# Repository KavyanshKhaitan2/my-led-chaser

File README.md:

# my-led-chaser
Just a simple LED chaser I made using the guides for Blinky @ Hack Club Blueprint.
# PCB View

# JLCPCB Order page

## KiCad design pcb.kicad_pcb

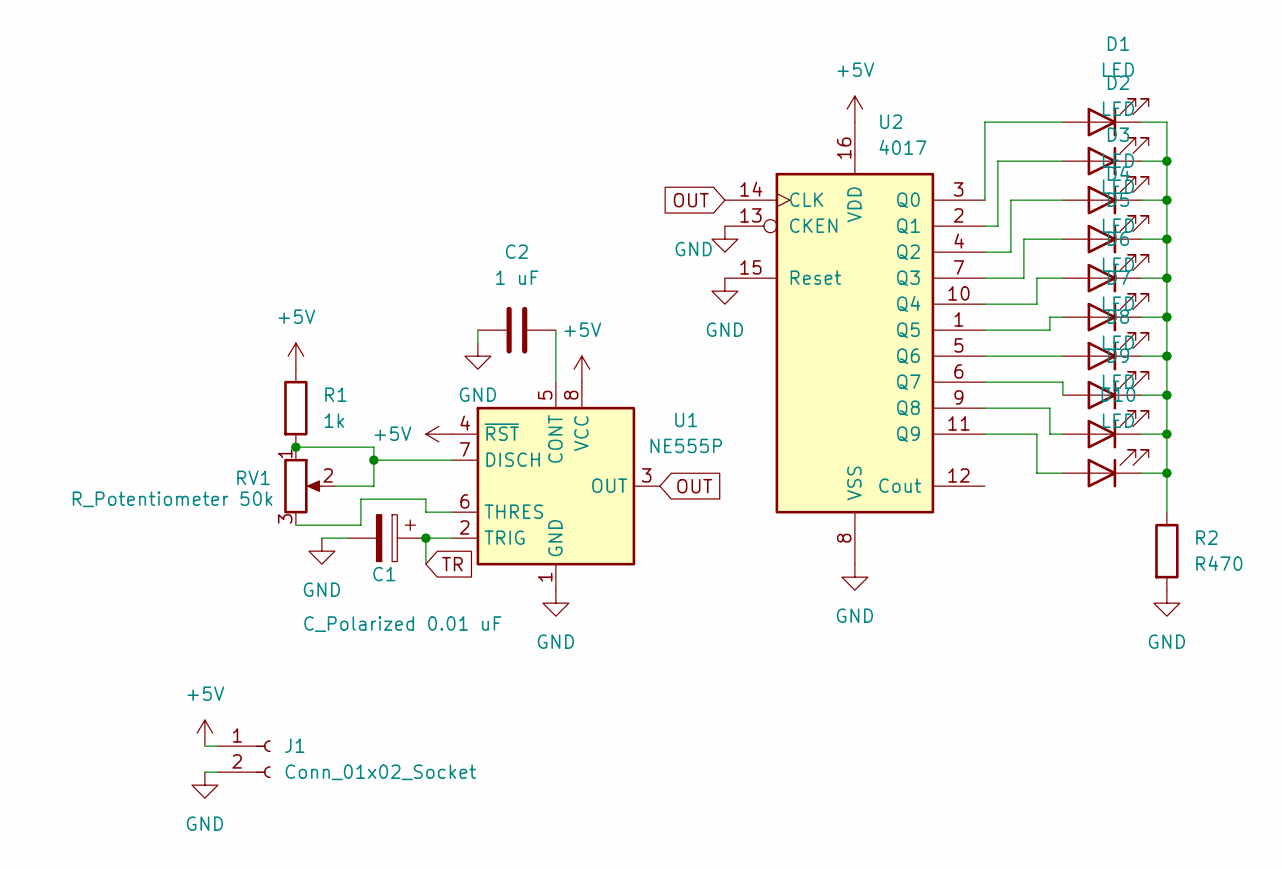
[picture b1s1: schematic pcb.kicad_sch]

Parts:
C1: C_Polarized 0.01 uF; CP_Radial_D5.0mm_P2.00mm
C2: 1 uF; C_Disc_D7.5mm_W2.5mm_P5.00mm
D1, D2, D3, D4, D5, D6, D7, D8, D9, D10: LED; LED_D3.0mm
J1: Conn_01x02_Socket; PinHeader_1x02_P2.54mm_Vertical
R1: 1k; R_Axial_DIN0207_L6.3mm_D2.5mm_P7.62mm_Horizontal
R2: R470; R_Axial_DIN0207_L6.3mm_D2.5mm_P7.62mm_Horizontal
RV1: R_Potentiometer 50k; Potentiometer_Vishay_T93YA_Vertical
U1: NE555P; DIP-8_W7.62mm
U2: 4017; N16

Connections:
+5V: J1.1, R1.1, U1.4 (~RST), U1.8 (VCC), U2.16 (VDD)
GND: C1.2, C2.1, J1.2, R2.2, U1.1 (GND), U2.8 (VSS), U2.13 (CKEN), U2.15 (Reset)
unnamed: D1.2 (A), U2.3 (Q0)
unnamed: D1.1 (K), D2.1 (K), D3.1 (K), D4.1 (K), D5.1 (K), D6.1 (K), D7.1 (K), D8.1 (K), D9.1 (K), D10.1 (K), R2.1
unnamed: D2.2 (A), U2.2 (Q1)
unnamed: D3.2 (A), U2.4 (Q2)
unnamed: D4.2 (A), U2.7 (Q3)
unnamed: D5.2 (A), U2.10 (Q4)
unnamed: D6.2 (A), U2.1 (Q5)
unnamed: D7.2 (A), U2.5 (Q6)
unnamed: D8.2 (A), U2.6 (Q7)
unnamed: D9.2 (A), U2.9 (Q8)
unnamed: D10.2 (A), U2.11 (Q9)
unnamed: C2.2, U1.5 (CONT)
unnamed: R1.2, RV1.1, RV1.2, U1.7 (DISCH)
unnamed: RV1.3, U1.6 (THRES)
OUT: U1.3 (OUT), U2.14 (CLK)
TR: C1.1, U1.2 (TRIG)

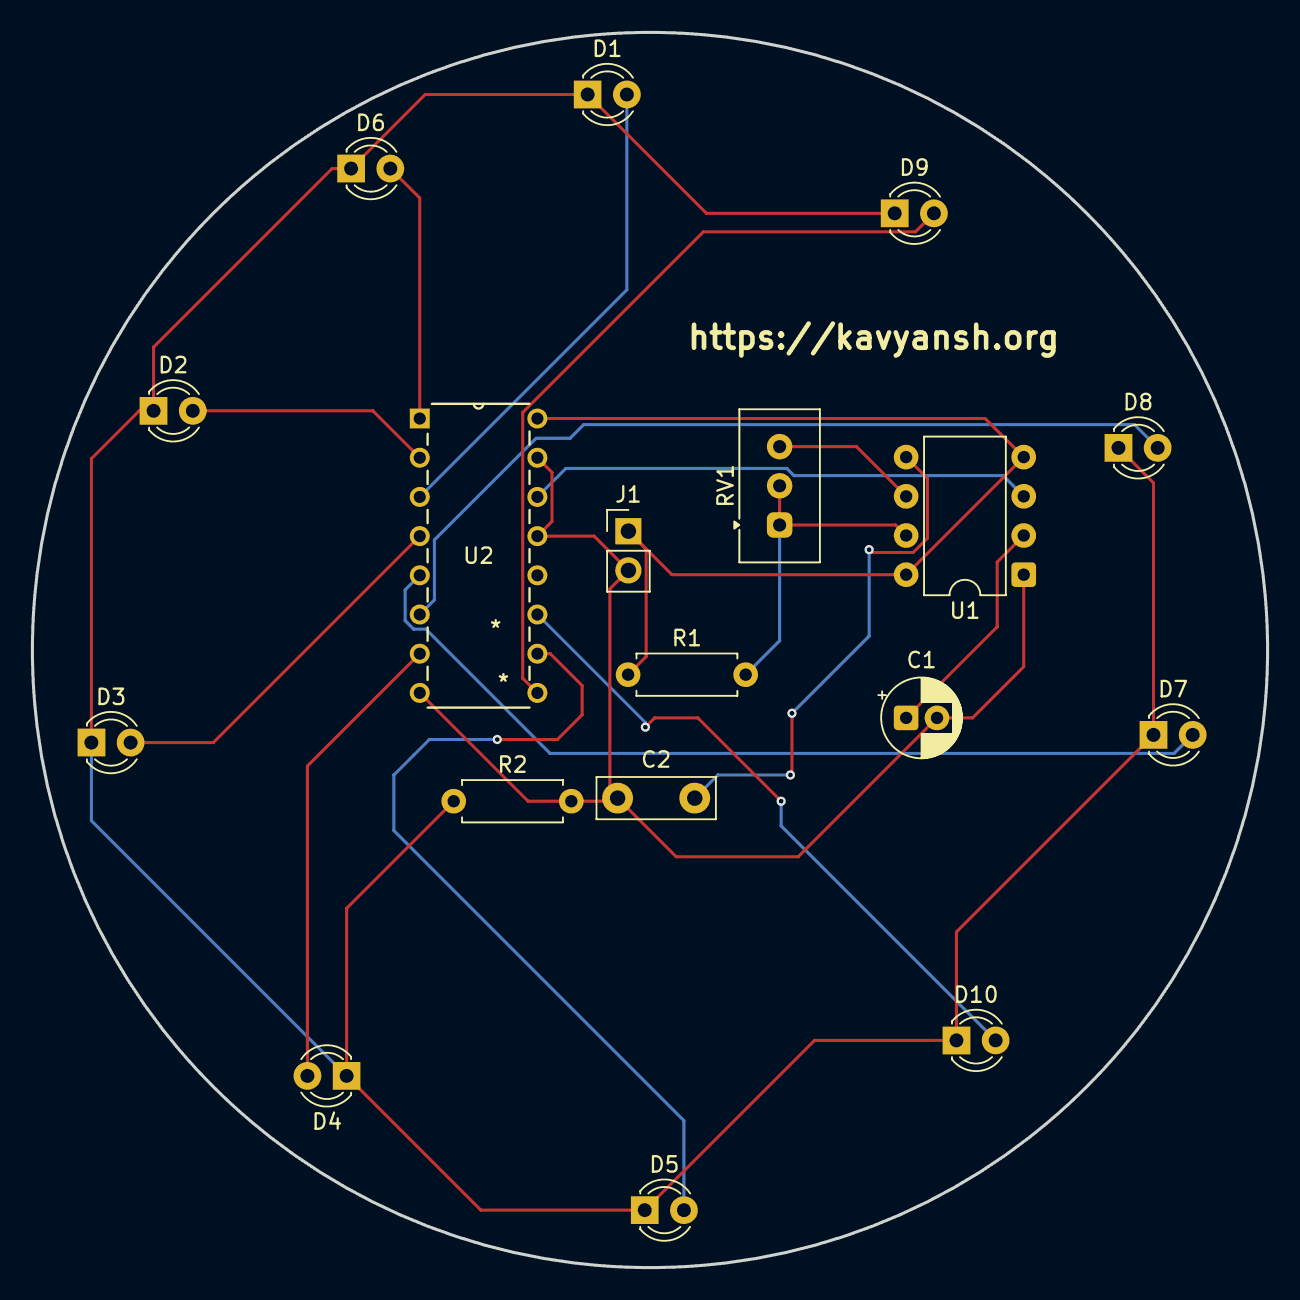
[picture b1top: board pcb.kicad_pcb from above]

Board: 2 copper layers, 80.0 x 80.0 mm, 18 parts (0 on the bottom side), 18 nets.

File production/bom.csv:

Designator,Footprint,Quantity,Value,LCSC Part #
C1,CP_Radial_D5.0mm_P2.00mm,1,C_Polarized 0.01 uF,
C2,C_Disc_D7.5mm_W2.5mm_P5.00mm,1,1 uF,
"D1, D10, D2, D3, D4, D5, D6, D7, D8, D9",LED_D3.0mm,10,LED,
J1,PinHeader_1x02_P2.54mm_Vertical,1,Conn_01x02_Socket,
R1,R_Axial_DIN0207_L6.3mm_D2.5mm_P7.62mm_Horizontal,1,1k,
R2,R_Axial_DIN0207_L6.3mm_D2.5mm_P7.62mm_Horizontal,1,R470,
RV1,Potentiometer_Vishay_T93YA_Vertical,1,R_Potentiometer 50k,
U1,DIP-8_W7.62mm,1,NE555P,
U2,N16,1,4017,

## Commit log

2026-02-20 Init 2
2026-02-20 add image
